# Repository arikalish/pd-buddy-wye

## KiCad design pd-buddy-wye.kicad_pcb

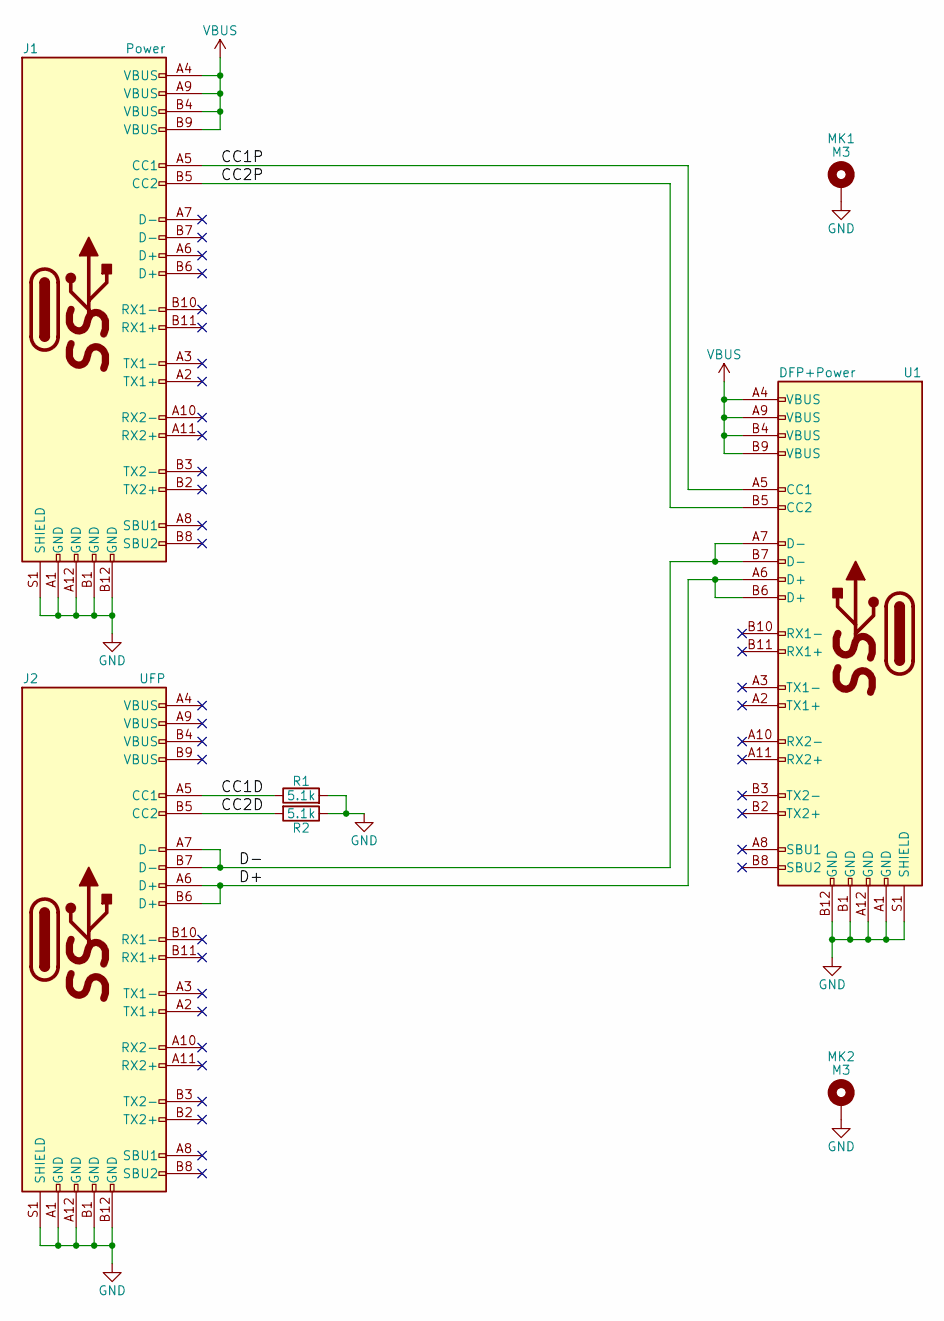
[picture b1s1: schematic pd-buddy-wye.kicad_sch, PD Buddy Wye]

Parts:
J1: Power; USB_C_Receptacle_Amphenol_12401610E4-2A
J2: UFP; USB_C_Receptacle_Amphenol_12401610E4-2A
MK1, MK2: M3; MountingHole_3.2mm_M3_Pad_Via
R1, R2: 5.1k; R_0805_2012Metric_Pad1.20x1.40mm_HandSolder
U1: DFP+Power; USB_C_Receptacle_Amphenol_12401610E4-2A

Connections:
/CC1D: J2.A5 (CC1), R1.1
/CC1P: J1.A5 (CC1), U1.A5 (CC1)
/CC2D: J2.B5 (CC2), R2.2
/CC2P: J1.B5 (CC2), U1.B5 (CC2)
/D+: J2.A6 (D+), J2.B6 (D+), U1.A6 (D+), U1.B6 (D+)
/D-: J2.A7 (D-), J2.B7 (D-), U1.A7 (D-), U1.B7 (D-)
GND: J1.A1 (GND), J1.A12 (GND), J1.B1 (GND), J1.B12 (GND), J1.S1 (SHIELD), J2.A1 (GND), J2.A12 (GND), J2.B1 (GND), J2.B12 (GND), J2.S1 (SHIELD), MK1.1, MK2.1, R1.2, R2.1, U1.A1 (GND), U1.A12 (GND), U1.B1 (GND), U1.B12 (GND), U1.S1 (SHIELD)
VBUS: J1.A4 (VBUS), J1.A9 (VBUS), J1.B4 (VBUS), J1.B9 (VBUS), U1.A4 (VBUS), U1.A9 (VBUS), U1.B4 (VBUS), U1.B9 (VBUS)

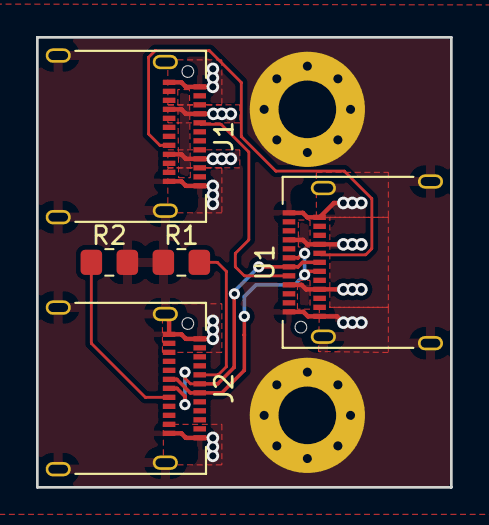
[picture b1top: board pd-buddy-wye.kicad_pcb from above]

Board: 2 copper layers, 23.0 x 25.0 mm, 7 parts (0 on the bottom side), 8 nets.

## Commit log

2025-05-30 Update to KiCad 8 and add PDF
2025-06-07 v2.0: Use receptacles
2025-06-13 Update PDF and gitignore
